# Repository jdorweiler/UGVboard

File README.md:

UGVboard
========

Unmanned ground vehicle board for chipkit Max32

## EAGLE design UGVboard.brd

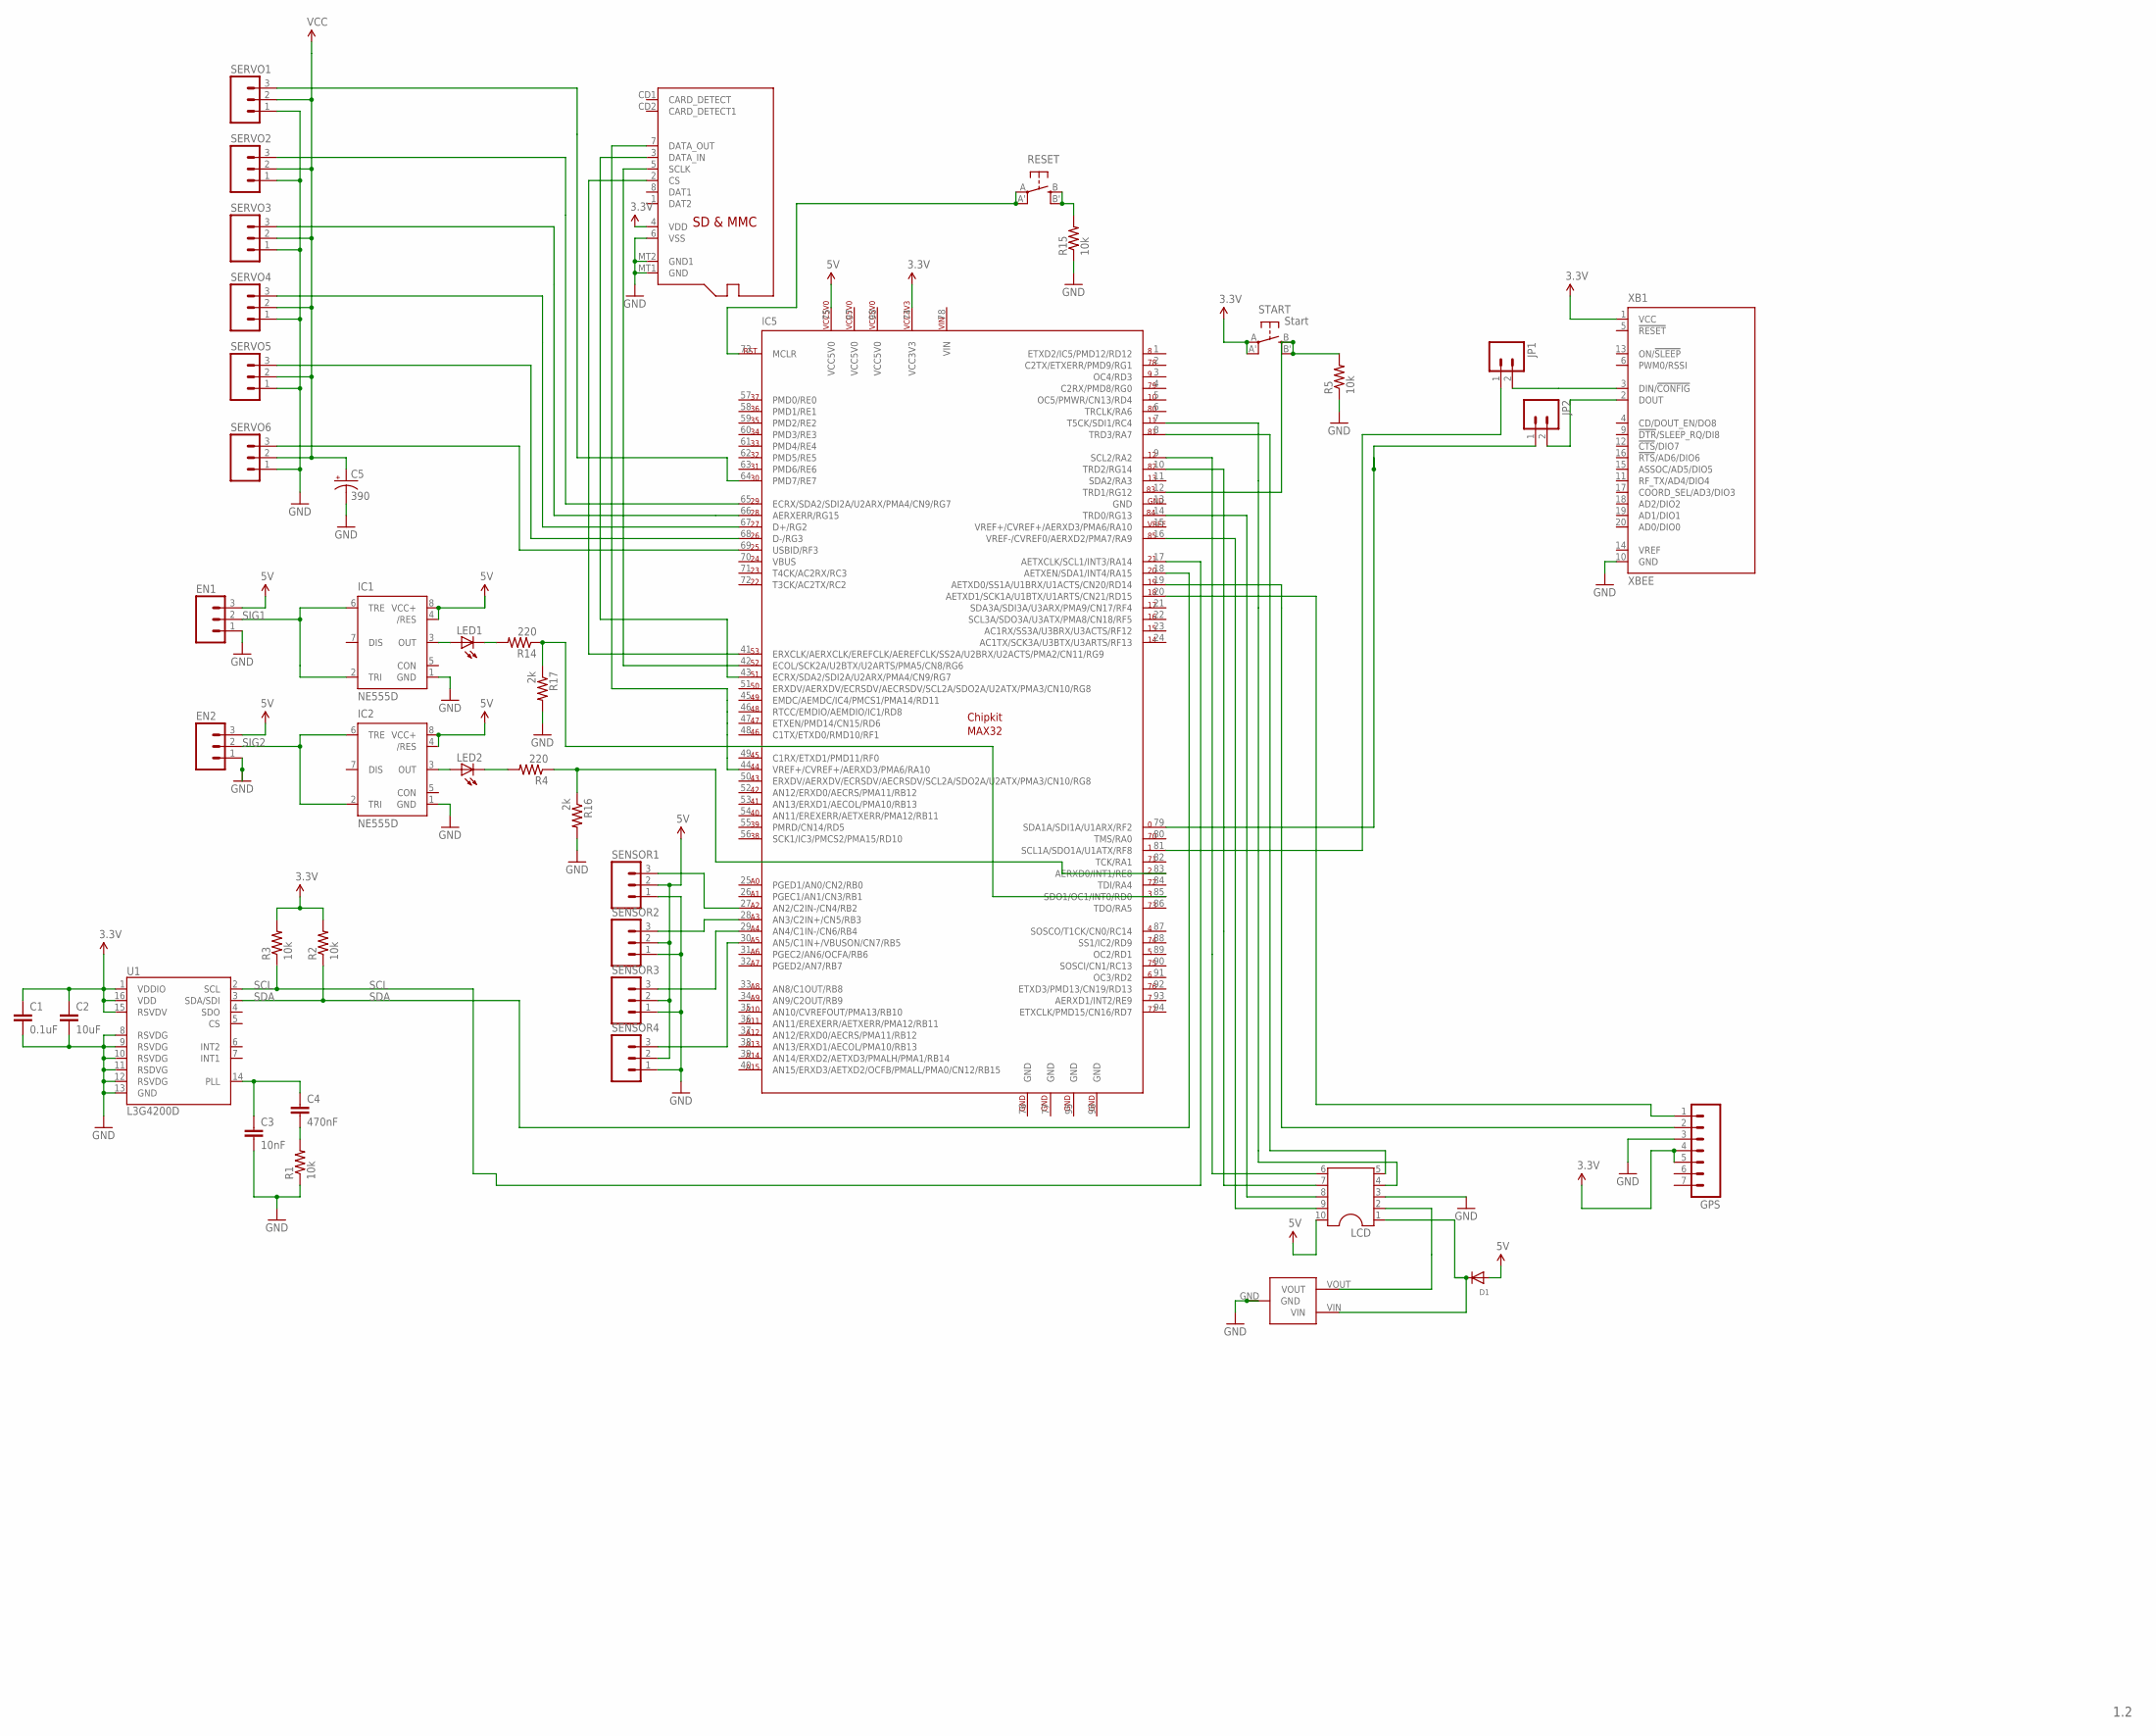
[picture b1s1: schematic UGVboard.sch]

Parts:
C1: 0.1uF; 0402-CAP
C2: 10uF; 1206
C3: 10nF; 0402-CAP
C4: 470nF; 0402-CAP
C5: 390; E3,5-8
D1: DIODESOD-323F; SOD-323F
EN1, EN2: M031X03_NO_SILK; 1X03_NO_SILK
GPS: M07; 1X07
IC1, IC2: NE555D; SO08
IC5: CHIPKIT_MAX_CONNECT; CHIPKIT_MAX32_CONNECT
JP1, JP2: M02PTH; 1X02
LCD: DIL10
LED1, LED2: LED0603; LED-0603
POT: POT2
R1, R2, R3, R5, R15: 10k; 0402-RES
R4, R14: 220; 0402-RES
R16, R17: 2k; 0402-RES
RESET: SPST_TACT-EVQQ2; EVQ-Q2
SDCARD: MICROSD
SENSOR1, SENSOR2, SENSOR3, SENSOR4: M03PTH; 1X03
SERVO1, SERVO2, SERVO3, SERVO4, SERVO5, SERVO6: M031X03_NO_SILK; 1X03_NO_SILK
START: Start; EVQ-Q2
U1: L3G4200D; LGA16-4X4
XB1: XBEE

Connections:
5V: D1.A, EN1.3, EN2.3, IC1.4 (/RES), IC1.8 (VCC+), IC2.4 (/RES), IC2.8 (VCC+), IC5.75 (VCC5V0), LCD.10, SENSOR1.2, SENSOR2.2, SENSOR3.2, SENSOR4.2
A2: IC5.27 (AN2/C2IN-/CN4/RB2), SENSOR1.3
A3: IC5.28 (AN3/C2IN+/CN5/RB3), SENSOR2.3
A4: IC5.29 (AN4/C1IN-/CN6/RB4), SENSOR3.3
A5: IC5.30 (AN5/C1IN+/VBUSON/CN7/RB5), SENSOR4.3
D2: IC5.83 (AERXD0/INT1/RE8), R4.1, R16.1
D3: IC5.85 (SDO1/OC1/INT0/RD0), R14.1, R17.1
D25: IC5.69 (USBID/RF3), SERVO6.3
D26: IC5.68 (D-/RG3), SERVO5.3
D27: IC5.67 (D+/RG2), SERVO4.3
D28: IC5.66 (AERXERR/RG15), SERVO3.3
D29: IC5.65 (ECRX/SDA2/SDI2A/U2ARX/PMA4/CN9/RG7), SERVO2.3
D30: IC5.64 (PMD7/RE7), SERVO1.3
D44: IC5.44 (VREF+/CVREF+/AERXD3/PMA6/RA10), SDCARD.7 (DATA_OUT)
D51: IC5.43 (ECRX/SDA2/SDI2A/U2ARX/PMA4/CN9/RG7), SDCARD.3 (DATA_IN)
D52: IC5.42 (ECOL/SCK2A/U2BTX/U2ARTS/PMA5/CN8/RG6), SDCARD.5 (SCLK)
D53: IC5.41 (ERXCLK/AERXCLK/EREFCLK/AEREFCLK/SS2A/U2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), SDCARD.2 (CS)
D83: IC5.12 (TRD1/RG12), R5.2, START.B (S), START.B' (S1)
unnamed: IC5.14 (TRD0/RG13), LCD.8
unnamed: IC5.7 (T5CK/SDI1/RC4), LCD.4
unnamed: IC5.16 (VREF-/CVREF0/AERXD2/PMA7/RA9), LCD.9
unnamed: IC1.3 (OUT), LED1.A
unnamed: LED1.C, R14.2
unnamed: LED2.C, R4.2
unnamed: IC2.3 (OUT), LED2.A
unnamed: JP1.2, XB1.3 (DIN/!CONFIG)
unnamed: JP2.2, XB1.2 (DOUT)
unnamed: IC5.9 (SCL2/RA2), LCD.6
unnamed: IC5.10 (TRD2/RG14), LCD.7
unnamed: D1.C, LCD.1, POT.VIN
unnamed: LCD.2, POT.VOUT
unnamed: IC5.8 (TRD3/RA7), LCD.5
unnamed: R15.2, RESET.B (S), RESET.B' (S1)
PLL: C3.1, C4.1, U1.14 (PLL); also elsewhere on the board
PLL-2: C4.2, R1.2
RST: IC5.73 (MCLR), RESET.A, RESET.A' (P1)
SCK: GPS.1, IC5.20 (AETXD1/SCK1A/U1BTX/U1ARTS/CN21/RD15)
SCL: IC5.17 (AETXCLK/SCL1/INT3/RA14), R3.1, U1.2 (SCL); also elsewhere on the board
SCL1: IC5.81 (SCL1A/SDO1A/U1ATX/RF8), JP1.1
SDA: IC5.18 (AETXEN/SDA1/INT4/RA15), R2.1, U1.3 (SDA/SDI); also elsewhere on the board
SDA1: IC5.79 (SDA1A/SDI1A/U1ARX/RF2), JP2.1
SIG1: EN1.2, IC1.2 (TRI), IC1.6 (TRE)
SIG2: EN2.2, IC2.2 (TRI), IC2.6 (TRE)
SS1: GPS.2, IC5.19 (AETXD0/SS1A/U1BRX/U1ACTS/CN20/RD14)
VCC: C5.+, SERVO1.2, SERVO2.2, SERVO3.2, SERVO4.2, SERVO5.2, SERVO6.2
VCC5V0: IC5.97 (VCC5V0), IC5.98 (VCC5V0)
VIN: IC5.78 (VIN)

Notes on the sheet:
1.2

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
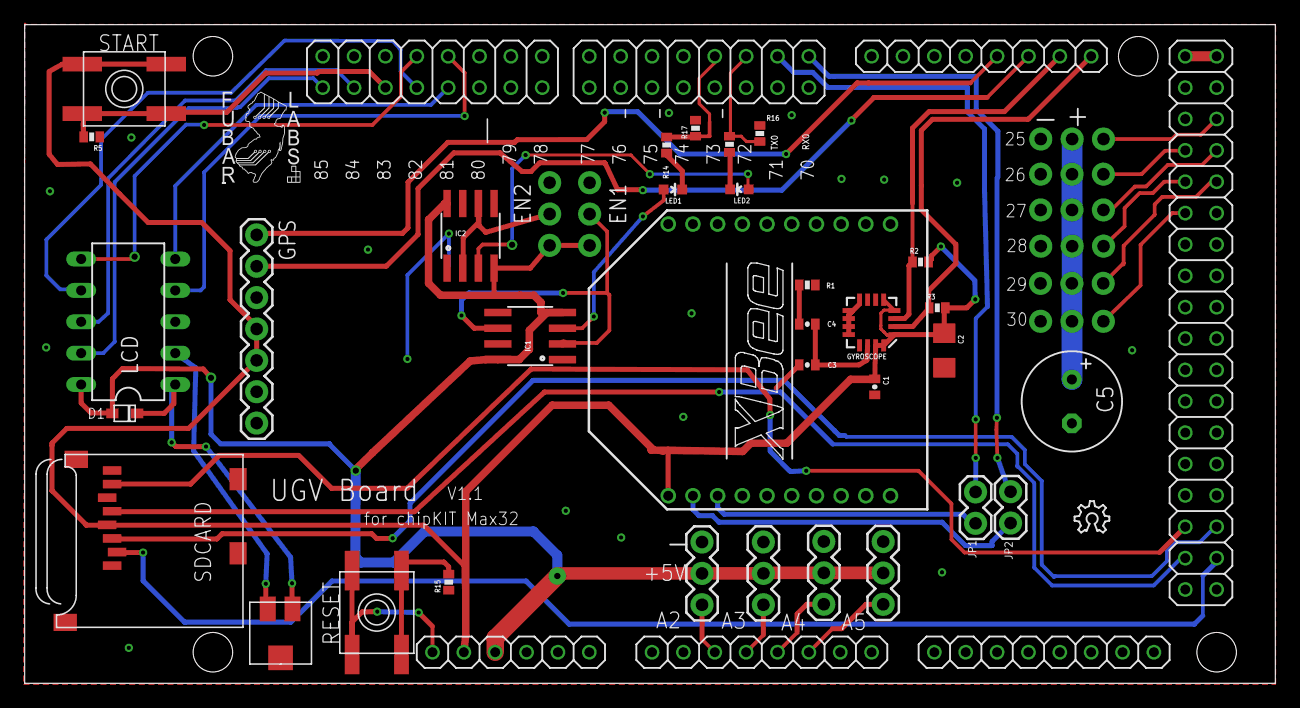
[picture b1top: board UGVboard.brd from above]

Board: 2 copper layers, 101.3 x 53.3 mm, 44 parts (0 on the bottom side), 48 nets.

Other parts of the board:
GYROSCOPE: L3G4200D; LGA16-4X4
U$8: OSHW_6X100_NOTEXT
U$10: FUBARLOGO3

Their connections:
PLL: GYROSCOPE.14; also elsewhere on the board
SCL: GYROSCOPE.2; also elsewhere on the board
SDA: GYROSCOPE.3; also elsewhere on the board

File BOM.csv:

"Part";"Value";"Device";"Package";"Description";"MF";"MPN";"OC_FARNELL";"OC_NEWARK";
"C1";"0.1uF";"CAP0402-CAP";"0402-CAP";"Capacitor";"";"";"";"";
"C2";"10uF";"CAP1206";"1206";"Capacitor";"";"";"";"";
"C3";"10nF";"CAP0402-CAP";"0402-CAP";"Capacitor";"";"";"";"";
"C4";"470nF";"CAP0402-CAP";"0402-CAP";"Capacitor";"";"";"";"";
"C5";"390";"CPOL-USE3.5-8";"E3,5-8";"POLARIZED CAPACITOR, American symbol";"";"";"";"";
"D1";"";"DIODESOD-323F";"SOD-323F";"Diode";"";"";"";"";
"EN1";"";"M031X03_NO_SILK";"1X03_NO_SILK";"Header 3";"";"";"";"";
"EN2";"";"M031X03_NO_SILK";"1X03_NO_SILK";"Header 3";"";"";"";"";
"GPS";"";"M07";"1X07";"Header 7";"";"";"";"";
"GYROSCOPE";"L3G4200D";"L3G4200D";"LGA16-4X4";"L3G4200D Three-axis, digital output gyroscope";"";"";"";"";
"IC1";"NE555D";"NE555D";"SO08";"General purpose bipolar Timer";"";"";"";"";
"IC2";"NE555D";"NE555D";"SO08";"General purpose bipolar Timer";"";"";"";"";
"IC5";"";"CHIPKIT_MAX_CONNECT";"CHIPKIT_MAX32_CONNECT";"The chipKIT? Max32? is based on the popular Arduino? open source hardware prototyping platform but adds the performance of the Microchip PIC32 microcontroller. The Max32 is the same form factor as the Arduino Mega board and is compatible with many Arduino? shields as well as larger shields for use with the Mega boards. It features a USB serial port interface for connection to the IDE and can be powered via USB or an external power supply.";"";"";"";"";
"JP1";"";"M02PTH";"1X02";"Header 2";"";"";"";"";
"JP2";"";"M02PTH";"1X02";"Header 2";"";"";"";"";
"LCD";"";"DIL10";"DIL10";"Dual In Line / Socket";"";"";"";"";
"LED1";"";"LED0603";"LED-0603";"LEDs";"";"";"";"";
"LED2";"";"LED0603";"LED-0603";"LEDs";"";"";"";"";
"POT";"";"POT2";"POT2";"";"";"";"";"";
"R1";"10k";"RESISTOR0402-RES";"0402-RES";"Resistor";"";"";"";"";
"R2";"10k";"RESISTOR0402-RES";"0402-RES";"Resistor";"";"";"";"";
"R3";"10k";"RESISTOR0402-RES";"0402-RES";"Resistor";"";"";"";"";
"R4";"220";"RESISTOR0402-RES";"0402-RES";"Resistor";"";"";"";"";
"R5";"10k";"RESISTOR0402-RES";"0402-RES";"Resistor";"";"";"";"";
"R14";"220";"RESISTOR0402-RES";"0402-RES";"Resistor";"";"";"";"";
"R15";"10k";"RESISTOR0402-RES";"0402-RES";"Resistor";"";"";"";"";
"R16";"2k";"RESISTOR0402-RES";"0402-RES";"Resistor";"";"";"";"";
"R17";"2k";"RESISTOR0402-RES";"0402-RES";"Resistor";"";"";"";"";
"RESET";"";"SPST_TACT-EVQQ2";"EVQ-Q2";"SMT 6mm switch, EVQQ2 series";"";"";"";"";
"SDCARD";"MICROSD";"MICROSD";"MICROSD";"Micro-SD / Transflash card holder with SPI pinout";"";"";"";"";
"SENSOR1";"";"M03PTH";"1X03";"Header 3";"";"";"";"";
"SENSOR2";"";"M03PTH";"1X03";"Header 3";"";"";"";"";
"SENSOR3";"";"M03PTH";"1X03";"Header 3";"";"";"";"";
"SENSOR4";"";"M03PTH";"1X03";"Header 3";"";"";"";"";
"SERVO1";"";"M031X03_NO_SILK";"1X03_NO_SILK";"Header 3";"";"";"";"";
"SERVO2";"";"M031X03_NO_SILK";"1X03_NO_SILK";"Header 3";"";"";"";"";
"SERVO3";"";"M031X03_NO_SILK";"1X03_NO_SILK";"Header 3";"";"";"";"";
"SERVO4";"";"M031X03_NO_SILK";"1X03_NO_SILK";"Header 3";"";"";"";"";
"SERVO5";"";"M031X03_NO_SILK";"1X03_NO_SILK";"Header 3";"";"";"";"";
"SERVO6";"";"M031X03_NO_SILK";"1X03_NO_SILK";"Header 3";"";"";"";"";
"START";"Start";"SPST_TACT-EVQQ2";"EVQ-Q2";"SMT 6mm switch, EVQQ2 series";"";"";"";"";
"XB1";"XBEE";"XBEE";"XBEE";"XBee (TM) /XBee-PRO(TM) OEM RF Modules";"";"XBP24-Z7UIT-004";"1751799";"34R5507";

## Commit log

2012-11-24 UGV board v1.1
2012-12-19 Updates to Board for v1.2
2012-12-25 v1.2 updates and cleaned up the schematic
2013-06-16 Added BOM
